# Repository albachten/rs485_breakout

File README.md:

# RS485 Breakout Board

* Includes 2 half-duplex RS485 interfaces
* Allows using CAT6 patch cables w/6 wires carrying power and one pair for communication
* Termination resistors were chosen to match 100ohm impedence of Cat5/6 Ethernet cables

[Schematic pdf](v1.0.RS485_breakout.pdf)

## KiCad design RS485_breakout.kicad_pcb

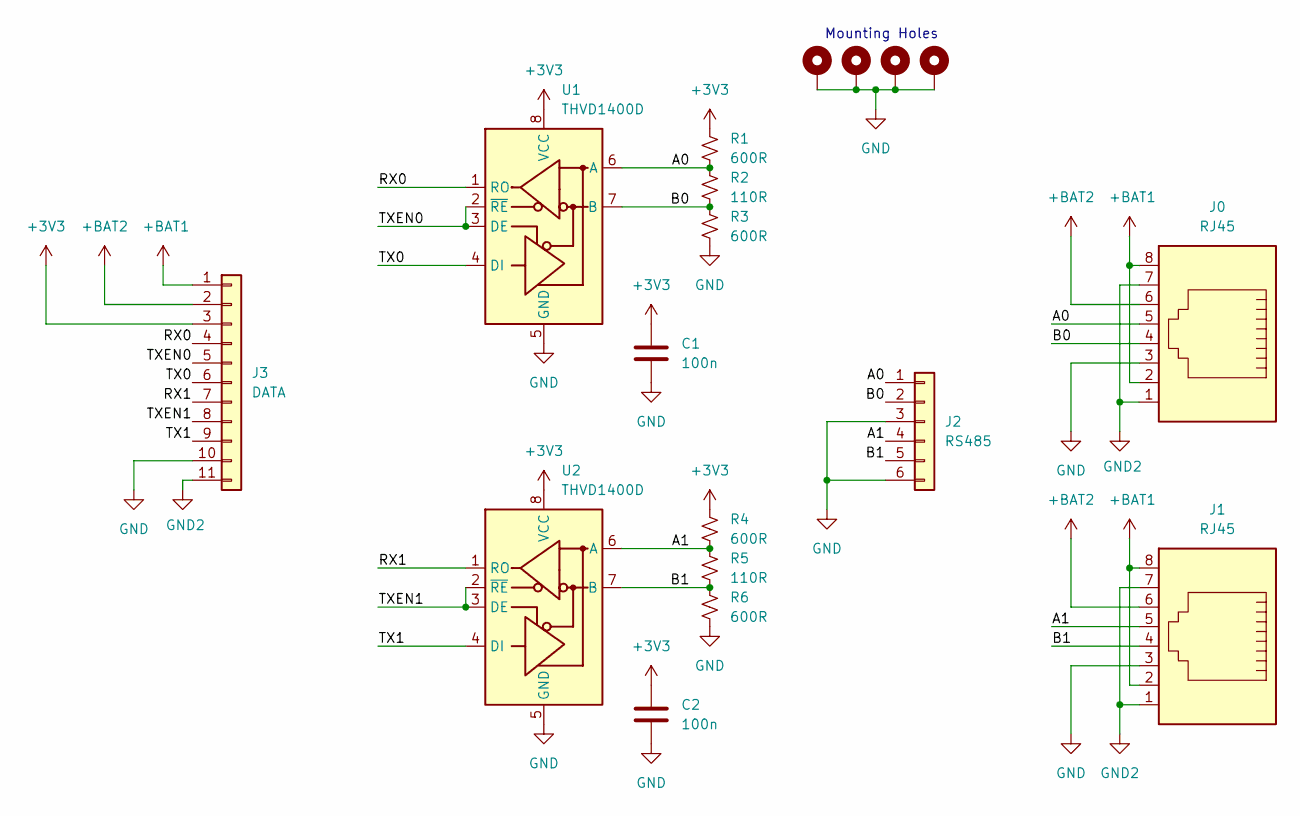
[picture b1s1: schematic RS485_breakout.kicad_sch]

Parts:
C1, C2: 100n; C_0805_2012Metric
H1, H2, H3, H4: MountingHole_Pad; MountingHole_3.2mm_M3_ISO7380_Pad
J0, J1: RJ45; RJ45_SS-700810-NF
J2: RS485; PinHeader_1x06_P2.54mm_Vertical
J3: DATA; PinHeader_1x11_P2.54mm_Vertical
R1, R3, R4, R6: 600R; R_0805_2012Metric
R2, R5: 110R; R_0805_2012Metric
U1, U2: THVD1400D; SOIC-8_3.9x4.9mm_P1.27mm

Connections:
+3V3: C1.1, C2.1, J3.3, R1.1, R4.1, U1.8 (VCC), U2.8 (VCC)
+BAT1: J0.2, J0.8, J1.2, J1.8, J3.1
+BAT2: J0.6, J1.6, J3.2
/A0: J0.5, J2.1, R1.2, R2.1, U1.6 (A)
/A1: J1.5, J2.4, R4.2, R5.1, U2.6 (A)
/B0: J0.4, J2.2, R2.2, R3.1, U1.7 (B)
/B1: J1.4, J2.5, R5.2, R6.1, U2.7 (B)
/RX0: J3.4, U1.1 (RO)
/RX1: J3.7, U2.1 (RO)
/TX0: J3.6, U1.4 (DI)
/TX1: J3.9, U2.4 (DI)
/TXEN0: J3.5, U1.2 (~RE), U1.3 (DE)
/TXEN1: J3.8, U2.2 (~RE), U2.3 (DE)
GND: C1.2, C2.2, H1.1, H2.1, H3.1, H4.1, J0.3, J1.3, J2.3, J2.6, J3.10, R3.2, R6.2, U1.5 (GND), U2.5 (GND)
GND2: J0.1, J0.7, J1.1, J1.7, J3.11

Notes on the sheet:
Mounting Holes

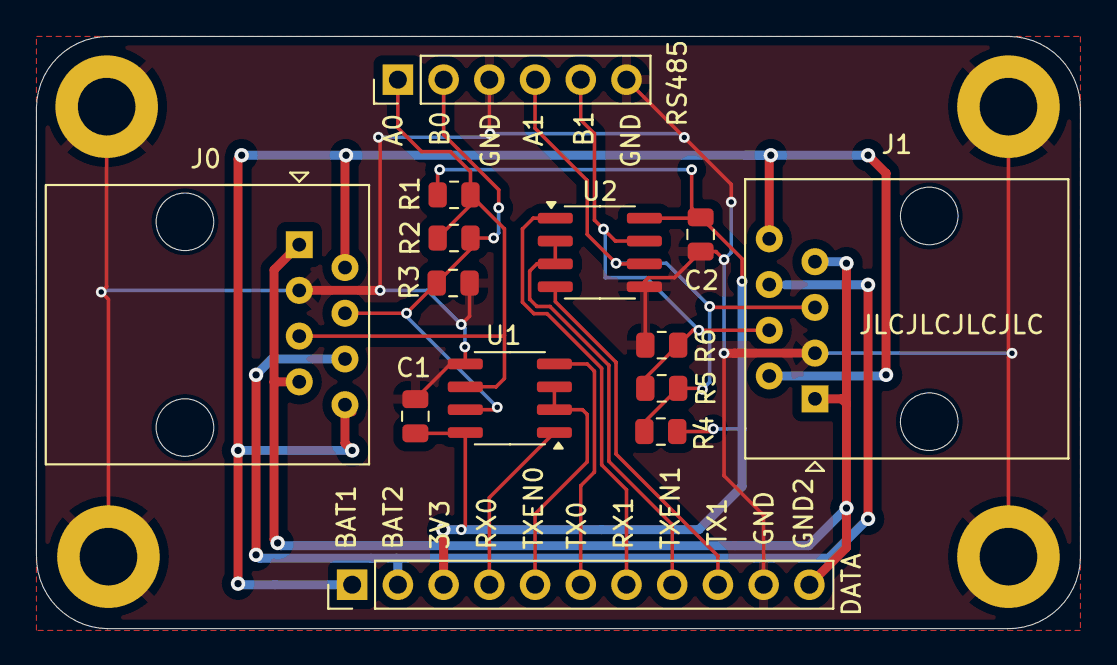
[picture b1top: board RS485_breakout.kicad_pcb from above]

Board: 2 copper layers, 58.0 x 32.9 mm, 18 parts (0 on the bottom side), 15 nets.

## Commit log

2024-06-23 v1.0
2024-06-23 Added images
